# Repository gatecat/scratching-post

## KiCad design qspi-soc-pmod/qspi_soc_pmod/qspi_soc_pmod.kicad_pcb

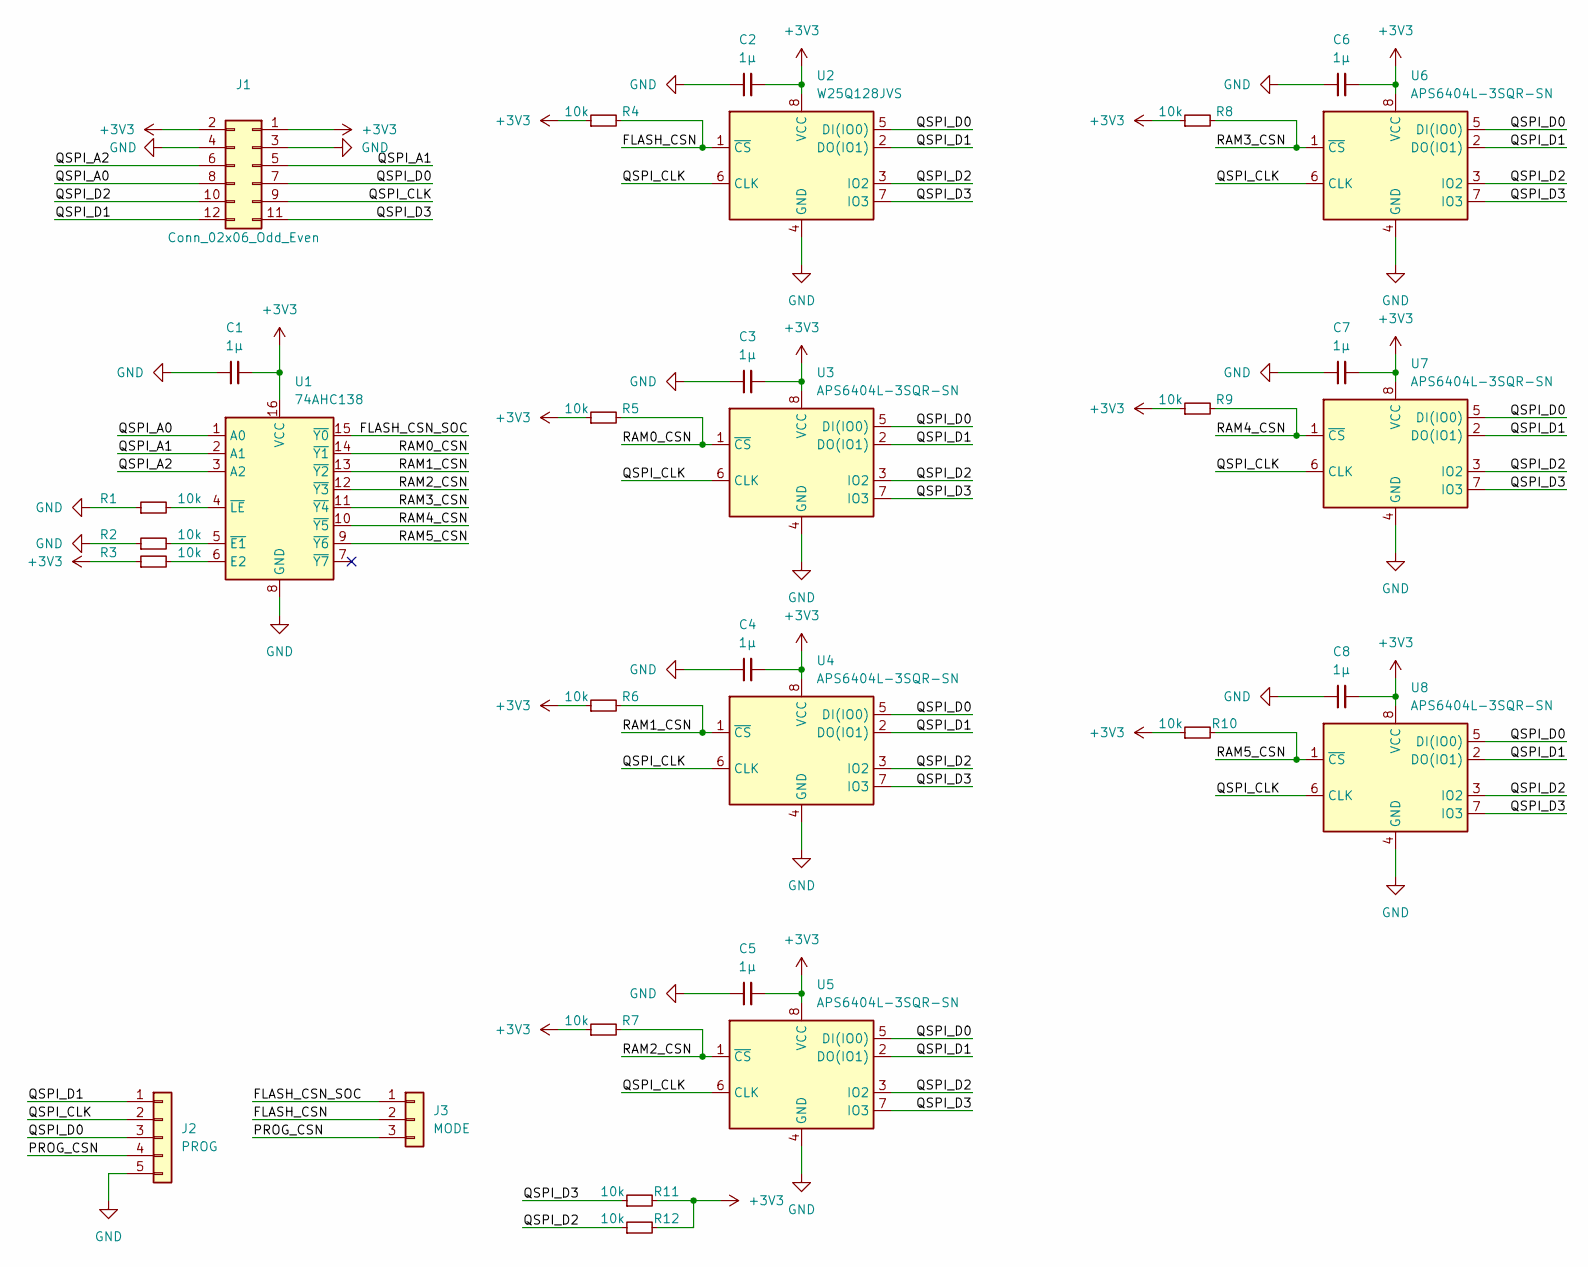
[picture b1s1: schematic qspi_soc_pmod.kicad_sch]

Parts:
C1, C2, C3, C4, C5, C6, C7: 1µ; C_0603_1608Metric
C8: 1µ; R_0603_1608Metric
J1: Conn_02x06_Odd_Even; PinHeader_2x06_P2.54mm_Horizontal
J2: PROG; PinHeader_1x05_P2.54mm_Vertical
J3: MODE; PinHeader_1x03_P2.54mm_Vertical
R1, R2, R3, R4, R5, R6, R7, R8, R9, R10, R11, R12: 10k; R_0603_1608Metric
U1: 74AHC138; SO-16_3.9x9.9mm_P1.27mm
U2: W25Q128JVS; SOIC-8_5.23x5.23mm_P1.27mm
U3, U4, U5, U6, U7, U8: APS6404L-3SQR-SN; SOIC-8_3.9x4.9mm_P1.27mm

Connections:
+3V3: C1.2, C2.2, C3.2, C4.2, C5.2, C6.2, C7.2, C8.2, J1.1, J1.2, R3.1, R4.1, R5.1, R6.1, R7.1, R8.1, R9.1, R10.1, R11.2, R12.2, U1.16 (VCC), U2.8 (VCC), U3.8 (VCC), U4.8 (VCC), U5.8 (VCC), U6.8 (VCC), U7.8 (VCC), U8.8 (VCC)
/FLASH_CSN: J3.2, R4.2, U2.1 (~CS)
/FLASH_CSN_SOC: J3.1, U1.15 (~Y0)
/PROG_CSN: J2.4, J3.3
/QSPI_A0: J1.8, U1.1 (A0)
/QSPI_A1: J1.5, U1.2 (A1)
/QSPI_A2: J1.6, U1.3 (A2)
/QSPI_CLK: J1.9, J2.2, U2.6 (CLK), U3.6 (CLK), U4.6 (CLK), U5.6 (CLK), U6.6 (CLK), U7.6 (CLK), U8.6 (CLK)
/QSPI_D0: J1.7, J2.3, U2.5 (DI(IO0)), U3.5 (DI(IO0)), U4.5 (DI(IO0)), U5.5 (DI(IO0)), U6.5 (DI(IO0)), U7.5 (DI(IO0)), U8.5 (DI(IO0))
/QSPI_D1: J1.12, J2.1, U2.2 (DO(IO1)), U3.2 (DO(IO1)), U4.2 (DO(IO1)), U5.2 (DO(IO1)), U6.2 (DO(IO1)), U7.2 (DO(IO1)), U8.2 (DO(IO1))
/QSPI_D2: J1.10, R12.1, U2.3 (IO2), U3.3 (IO2), U4.3 (IO2), U5.3 (IO2), U6.3 (IO2), U7.3 (IO2), U8.3 (IO2)
/QSPI_D3: J1.11, R11.1, U2.7 (IO3), U3.7 (IO3), U4.7 (IO3), U5.7 (IO3), U6.7 (IO3), U7.7 (IO3), U8.7 (IO3)
/RAM0_CSN: R5.2, U1.14 (~Y1), U3.1 (~CS)
/RAM1_CSN: R6.2, U1.13 (~Y2), U4.1 (~CS)
/RAM2_CSN: R7.2, U1.12 (~Y3), U5.1 (~CS)
/RAM3_CSN: R8.2, U1.11 (~Y4), U6.1 (~CS)
/RAM4_CSN: R9.2, U1.10 (~Y5), U7.1 (~CS)
/RAM5_CSN: R10.2, U1.9 (~Y6), U8.1 (~CS)
GND: C1.1, C2.1, C3.1, C4.1, C5.1, C6.1, C7.1, C8.1, J1.3, J1.4, J2.5, R1.1, R2.1, U1.8 (GND), U2.4 (GND), U3.4 (GND), U4.4 (GND), U5.4 (GND), U6.4 (GND), U7.4 (GND), U8.4 (GND)
unnamed: R1.2, U1.4 (~LE)
unnamed: R2.2, U1.5 (~E1)
unnamed: R3.2, U1.6 (E2)

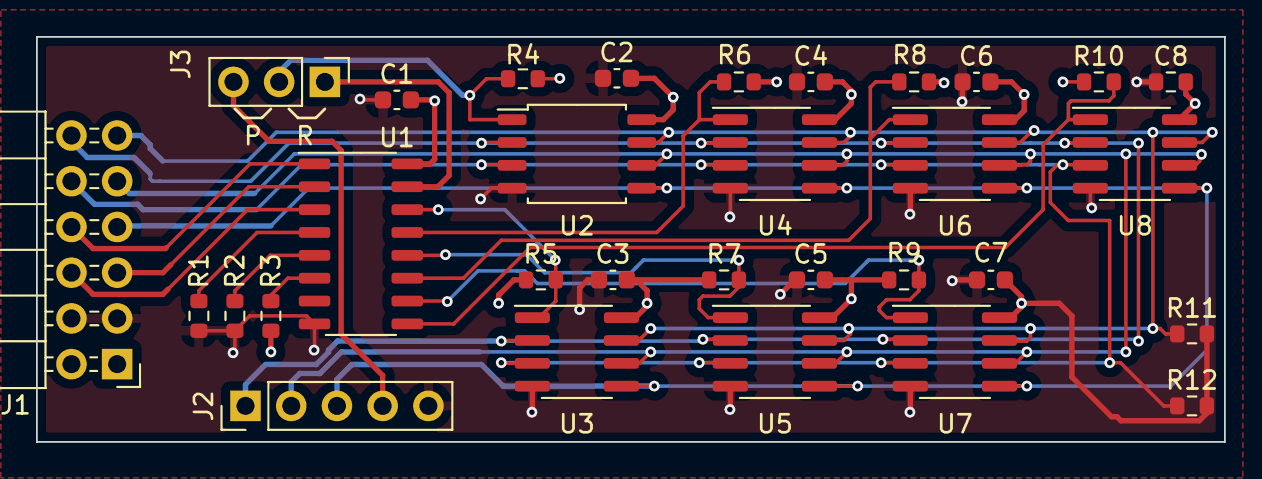
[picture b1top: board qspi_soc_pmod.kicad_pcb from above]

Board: 4 copper layers, 66.0 x 22.5 mm, 31 parts (0 on the bottom side), 22 nets.

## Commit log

2022-01-10 Add Arlet6502 design for testing
2022-01-10 Add post-synthesis timing with Tas
2022-01-10 Add wrapper and PnR script
2022-01-10 Export LEF and DEF
2022-01-11 Write DEF for all cells
2022-01-12 Adding openrcx import
2022-01-12 Add post-pnr timing analysis
2022-01-14 Allow comparing postpnr/postsyn slack
2022-01-17 Minimal clock doubler
2022-01-17 Improved clock doubler
2022-01-17 Example using doubled clock to build a dual port ram
2022-01-17 Add some comments and a diagram
2022-01-18 Add small vex config for testing
2022-01-18 Add wrapper to test PnR
2022-01-19 Add custom VexRiscv config with JTAG
2022-01-19 Add cores from MPW4
2022-01-19 Add peripheral bits from lambdasoc; update imports
2022-01-19 Working on a wrapper for vexriscv
2022-01-19 Fix reset vector
2022-01-19 Start porting MPW4 SoC to Vex
2022-01-19 Add blinky software
2022-01-19 Update FPGA test pinout
2022-01-19 Add FPGA SoC (broken :nya_sad:)
2022-01-19 Add simulation test
2022-01-19 Switch back to sync resets for now
2022-01-19 Add OpenOCD config
2022-01-19 Post-synth simulation
2022-01-19 Add bare-minimum UART
2022-01-19 Attempt and fail to run C
2022-01-19 🐱: nyaa~
2022-01-19 Initial attempts at Linux...
2022-01-19 Throwing in more of the BIOS
2022-01-20 Working on CXXRTL SoC
2022-01-20 Add PC trace; disable SRAM bursts
2022-01-20 Update kernel patches
2022-01-20 Trying without xip
2022-01-20 Fix load
2022-01-20 Fix alignment
2022-01-21 WIP replace SPI flash with emulated ideal ROM
2022-01-21 Track stalled transactions
2022-01-21 Add VCD dumping
2022-01-21 Fix trap handler
2022-01-21 BIOS fixes
2022-01-21 Re-enable D$
2022-01-21 Update kernel patch set
2022-01-22 Add a platform timer
2022-01-22 Fix linux config
2022-01-22 Add system timer
2022-01-22 Patch update
2022-01-22 Add rootfs on flash
2022-01-23 Cleaner patch set, hopefully ready for upstream
2022-01-23 ASIC scripts to test
2022-01-25 Add stub ULX3S python
2022-01-25 Updated flash core
2022-01-25 Add updated UART core
2022-01-25 WIP ULX3S wrapper
2022-01-26 WIP ULX3S SoC
2022-01-26 SoC fixes
2022-01-26 Add UART
2022-01-26 WIP linux
2022-01-26 Misc debugging
2022-01-26 debug, 2
2022-01-26 Fix hyperram latency for PMOD
2022-01-27 Init sim flash to 0xFF
2022-01-27 Update patch set with BSS fix
2022-02-01 Get SoC working on HW
2022-02-02 Prototype new drivers approach
2022-02-02 Add more drivers
2022-02-02 Add SoC ID core
2022-02-03 Working on new sim infra
2022-02-03 Add sim box generation
2022-02-04 Reworking sim pt1
2022-02-04 Init SPI flash
2022-02-04 Working on hyperram model
2022-02-07 Add UART sim model
2022-02-07 Move ULX3S SoC to use 'orchard' cores
2022-02-07 Minor tidy
2022-02-07 Add bus monitor, fix hyperram
2022-02-08 Implement flash read ID
2022-02-08 Enter quad mode (temporarily breaks sim)
2022-02-08 Enable quad flash
2022-02-09 WIP integrating new HyperRAM
2022-02-10 memtest
2022-02-10 hyperram wip
2022-02-18 Update RAM init
2022-02-22 WIP DP aux
2022-02-22 Manchester decoder kinda works
2022-02-23 Working on AUX TX FSM
2022-02-23 Working on AUX TX PHY FSM
2022-02-23 TX FSM fixes
2022-02-24 WIP packet structure
2022-02-27 Work on upacket receiver fsm
2022-03-09 Working on upacket fsm
2022-03-09 Small read transaction works
2022-03-12 Refactor upacket testbench
2022-03-12 WIP I2C over AUX packets
2022-03-12 Add some tests for I2C over aux
2022-08-02 Initial synth script without memories
2022-08-02 Adding some basic memory rules for test purposes
2022-08-04 adding buffer chain simulation
2022-08-17 old sim stuff
2022-08-17 Setting out the basic primitive library
2022-08-17 WIP clbgen
2022-08-17 clbgen: Generic fraclut generator
2022-08-17 clb_gen: Work on a complex FF generator
2022-08-18 Basic multiplier mapping
2022-08-19 Adding config muxtree generator
2022-08-23 Adding a protoype LUTRAM implementation for area estimation
2022-08-23 Add without LUTRAM to compare
2022-08-24 Working on FABulous-compatible multiply decomposition
2022-08-25 FABulous RegFile mapping rules
2022-08-25 Add a wrapper for the FABulous multipliers
2022-08-30 fpga wip
2022-09-06 Working on improved DSP primitive
2022-09-09 Initial fabulous wrapper script
2022-09-09 Fix load script
2022-09-12 WIP bitstream loading
2022-09-13 switching to uart config
2022-09-14 testbench updates
2022-09-16 updates, switch back to parallel configuration
2022-09-23 mapping script for paper experiment
2022-09-26 initial techlib
2022-09-26 types
2022-09-26 Initial bel stuff
2022-09-26 some tile stuff
2022-09-27 working
2022-09-27 things
2022-09-28 Finish example switch matrix
2022-09-28 working on tile contents
2022-09-29 working on generating a boring regular tile first
2022-09-29 debugging
2022-09-29 fixing
2022-10-04 adding a CGRA elem for test purposes
2022-10-14 working on a CGRA tile
2022-10-14 tile gen fixes
2022-10-17 initial attempt (fails due to loops)
2022-11-12 WIP: muladd generator
2022-11-12 typo
2022-11-29 add outline
2022-11-29 wordline poly
2022-11-29 contacts
2022-11-29 outline of the bitcell itself
2022-11-29 add inverter gates
2022-11-29 add transmission gate
2022-11-29 'complete' and drc clean
2022-11-30 LEF patching, SPICE extracting magic
2022-11-30 add spice tb
2022-12-01 trying
2022-12-12 exploring RAM topologies
2022-12-13 test assembler script
2022-12-14 wip: testbench
2022-12-14 bunch of cgra fixes
2022-12-20 adding some constants for sky130
2022-12-20 bitcell update for sky130
2022-12-20 bits
2022-12-20 basic bitcell
2022-12-20 initial level restorer buf
2022-12-21 sky130 lef generation
2022-12-21 enlargen to fix pin access issue (wip)
2022-12-21 make pin access even easier
2022-12-21 initial word/bitline stuff
2022-12-21 compute hpwl
2022-12-21 do some optimisations
2022-12-21 move script
2022-12-21 new mux opt
2022-12-28 add config stuff for our modules
2022-12-30 update config for LUTRAM support
2023-01-03 restructuring
2023-01-03 working on building clbs
2023-01-04 working on CLB gen stuff
2023-01-09 working on a test config
2023-01-09 more fixes
2023-01-10 adding a toy benchmark
2023-01-16 schematic for qspi pmod
2023-01-16 QSPI PMOD PCB
2023-01-18 PCB update
2023-01-18 memory outline interface
2023-01-18 working on qspi
2023-01-18 adding shift register etc
2023-01-19 working on main memory fsm
2023-01-19 poke density stuff
2023-01-20 filling in various FSM parts
2023-01-20 fsm fixes
2023-01-20 working on sim model arch
2023-01-20 testing model integration
2023-01-20 filling in flash model
2023-01-20 adding test runner
2023-01-20 get SPI read test working
2023-01-20 adding a bunch of test coverage
2023-01-23 fix max burst limit
2023-03-08 adding CVA6 jtag test
2023-05-24 stub delta plugin
2023-05-25 fft testing
2023-05-25 explore dcst/dsct
2023-05-31 add plot
2023-12-29 sram test
2024-01-03 experiment: patch out power connections
2024-01-10 wip: sram
2024-01-11 tweaks and hacks...
2024-01-29 pnr script update
2024-02-10 tiny bringup script
2024-06-11 splittri
2025-06-22 stub
2025-06-22 servo
2025-06-30 skeleton
2025-06-30 Adding test SRAM
2025-07-04 add MemoryMap
2025-08-25 cvc testbench
2025-09-02 add top level wrapper for verilator
2025-09-02 wip: verilator
2025-09-04 tweak
2026-04-05 186 test
2026-04-05 blinky
2026-04-09 80x86 and build products
